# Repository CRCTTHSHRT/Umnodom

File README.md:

# Clever_Light
Схема управления диммером светодиодного светильника на основе ардуино

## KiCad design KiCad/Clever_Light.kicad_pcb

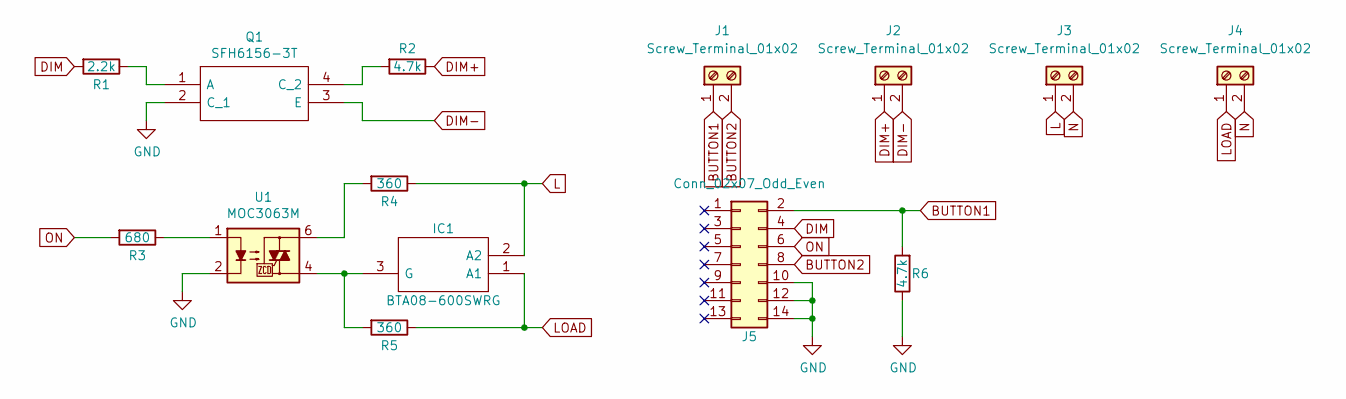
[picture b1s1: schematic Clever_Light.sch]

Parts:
IC1: BTA08-600SWRG; TO-220-3_Horizontal_TabDown; Mouser Part Number 511-BTA08-600SW
J1, J2, J3, J4: Screw_Terminal_01x02; TerminalBlock_KV301_1x02_P5.00mm_Horizontal
J5: Conn_02x07_Odd_Even; IDC-Header_2x07_P2.54mm_Vertical
Q1: SFH6156-3T; SMDIP-4_W9.53mm_Clearance8mm; Manufacturer_Part_Number SFH6156-3T; Mouser Part Number 782-SFH6156-3T
R1: 2.2k; R_1206_3216Metric
R2, R6: 4.7k; R_1206_3216Metric
R3: 680; R_1206_3216Metric
R4, R5: 360; R_2512_6332Metric_Pad1.52x3.35mm_HandSolder
U1: MOC3063M; DIP-6_W10.16mm_LongPads

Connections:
BUTTON1: J1.1, J5.2, R6.2
BUTTON2: J1.2, J5.8
DIM: J5.4, R1.2
DIM+: J2.1, R2.1
DIM-: J2.2, Q1.3 (E)
GND: J5.10, J5.12, J5.14, Q1.2 (C_1), R6.1, U1.2
L: IC1.2 (A2), J3.1, R4.1
LOAD: IC1.1 (A1), J4.1, R5.1
N: J3.2, J4.2
unnamed: IC1.3 (G), R5.2, U1.4
unnamed: Q1.1 (A), R1.1
unnamed: Q1.4 (C_2), R2.2
unnamed: R3.1, U1.1
unnamed: R4.2, U1.6
ON: J5.6, R3.2

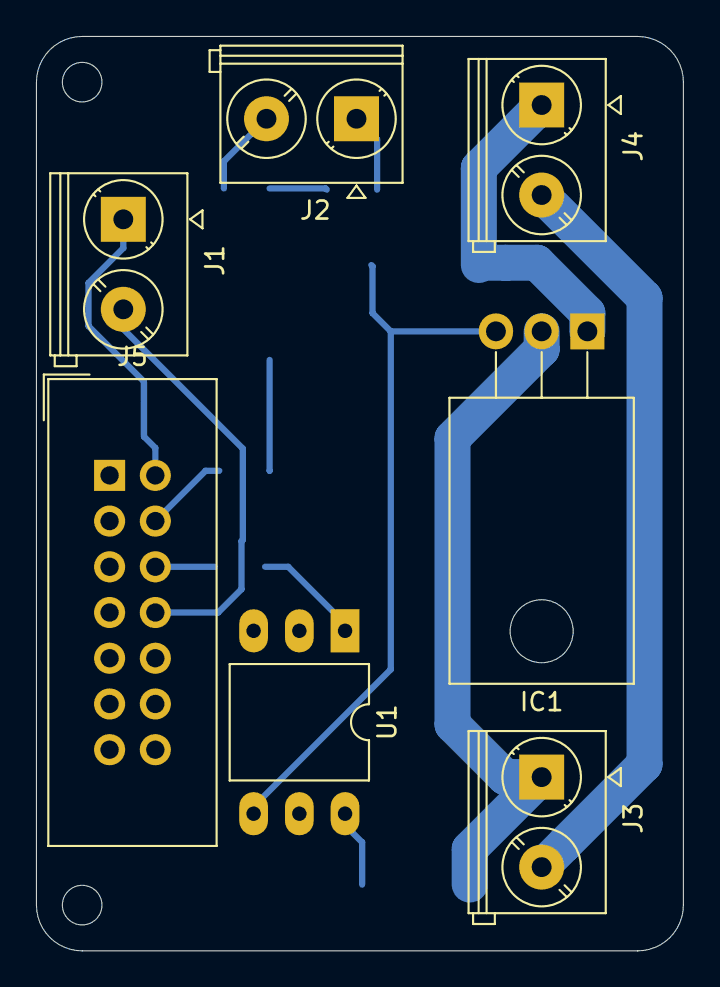
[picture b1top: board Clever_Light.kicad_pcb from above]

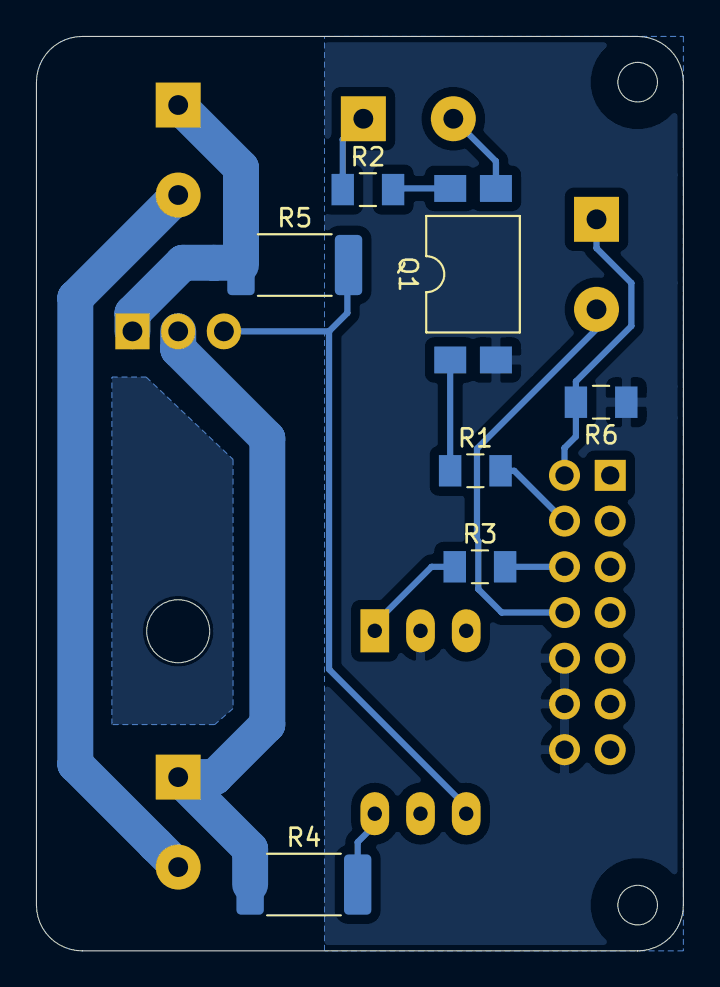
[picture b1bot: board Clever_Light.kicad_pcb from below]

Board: 2 copper layers, 35.9 x 50.8 mm, 14 parts (7 on the bottom side), 15 nets.

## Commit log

2019-07-22 Ардуиновский код и схема для SimulIDE
2019-08-10 Тестовый коммит, без понятия что происходит
2019-08-10 Новая структура файлов
2019-08-10 Схема
2019-08-10 Ридми файл
2019-08-11 Добавлены чертежи и файл сверловки
2019-08-13 правка пинов
2019-08-17 небольшая оптимизация
2019-08-17 Файлы сверловки
2019-08-18 Исправил глубину реза для фрезы d0.65
2019-08-18 Адаптировал под bootloader с WDT
2019-08-19 вдогонку
2019-12-31 Добавлен код для работы с 3 светодиодными лентами
2020-01-06 Кнопка теперь замыкается на землю
2020-01-06 Переназначены пины для управления лентами
2020-01-06 Исправлено поведение кнопки
